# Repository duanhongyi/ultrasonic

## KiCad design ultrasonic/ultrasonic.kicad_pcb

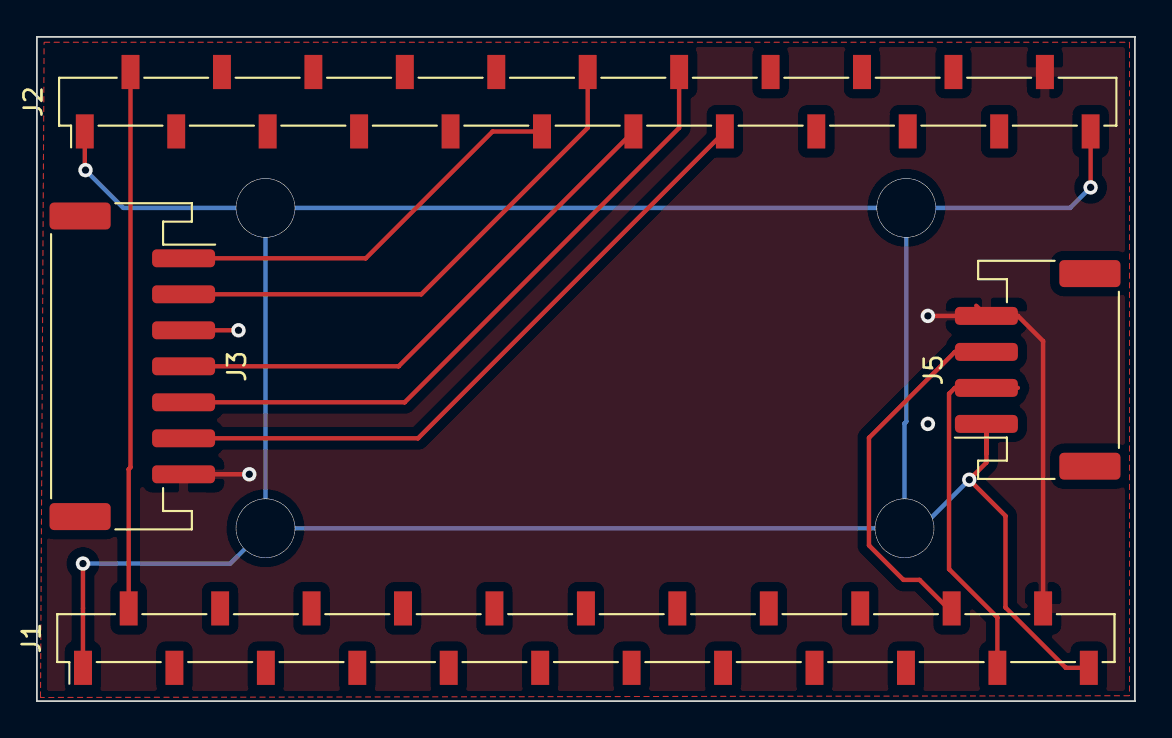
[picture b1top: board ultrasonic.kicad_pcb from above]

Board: 2 copper layers, 61.0 x 36.9 mm, 4 parts (0 on the bottom side), 10 nets.

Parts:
J1, J2: Conn_01x23_Female; PinSocket_1x23_P2.54mm_Vertical_SMD_Pin1Left
J3: Conn_01x07_Female; JST_PH_S7B-PH-SM4-TB_1x07-1MP_P2.00mm_Horizontal
J5: Conn_01x04_Male; JST_PH_S4B-PH-SM4-TB_1x04-1MP_P2.00mm_Horizontal

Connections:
+3V3: J1.2, J2.2
+5V: J1.22, J2.22, J3.7, J5.4
/IO17: J1.20, J5.3
/IO18: J1.21, J5.2
/IO35: J2.15, J3.6
/IO36: J2.14, J3.5
/IO37: J2.13, J3.4
/IO38: J2.12, J3.2
/IO39: J2.11, J3.1
GND: J1.1, J1.23, J2.1, J2.23, J3.3, J5.1

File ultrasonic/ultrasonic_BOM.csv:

"Comment","Description","Designator","Footprint","LibRef","Pins","Quantity","PartNumber","url",
"Conn_01x23_Female","desc","J1,","PinSocket_1x23_P2.54mm_Vertical_SMD_Pin1Right","libref","23","1","","",
"Conn_01x23_Female","desc","J2,","PinHeader_1x23_P2.54mm_Vertical_SMD_Pin1Left","libref","23","1","","",
"Conn_01x07_Female","desc","J3,","JST_PH_S7B-PH-SM4-TB_1x07-1MP_P2.00mm_Horizontal","libref","9","1","","",
"Conn_01x04_Male","desc","J5,","JST_PH_S4B-PH-SM4-TB_1x04-1MP_P2.00mm_Horizontal","libref","6","1","","",

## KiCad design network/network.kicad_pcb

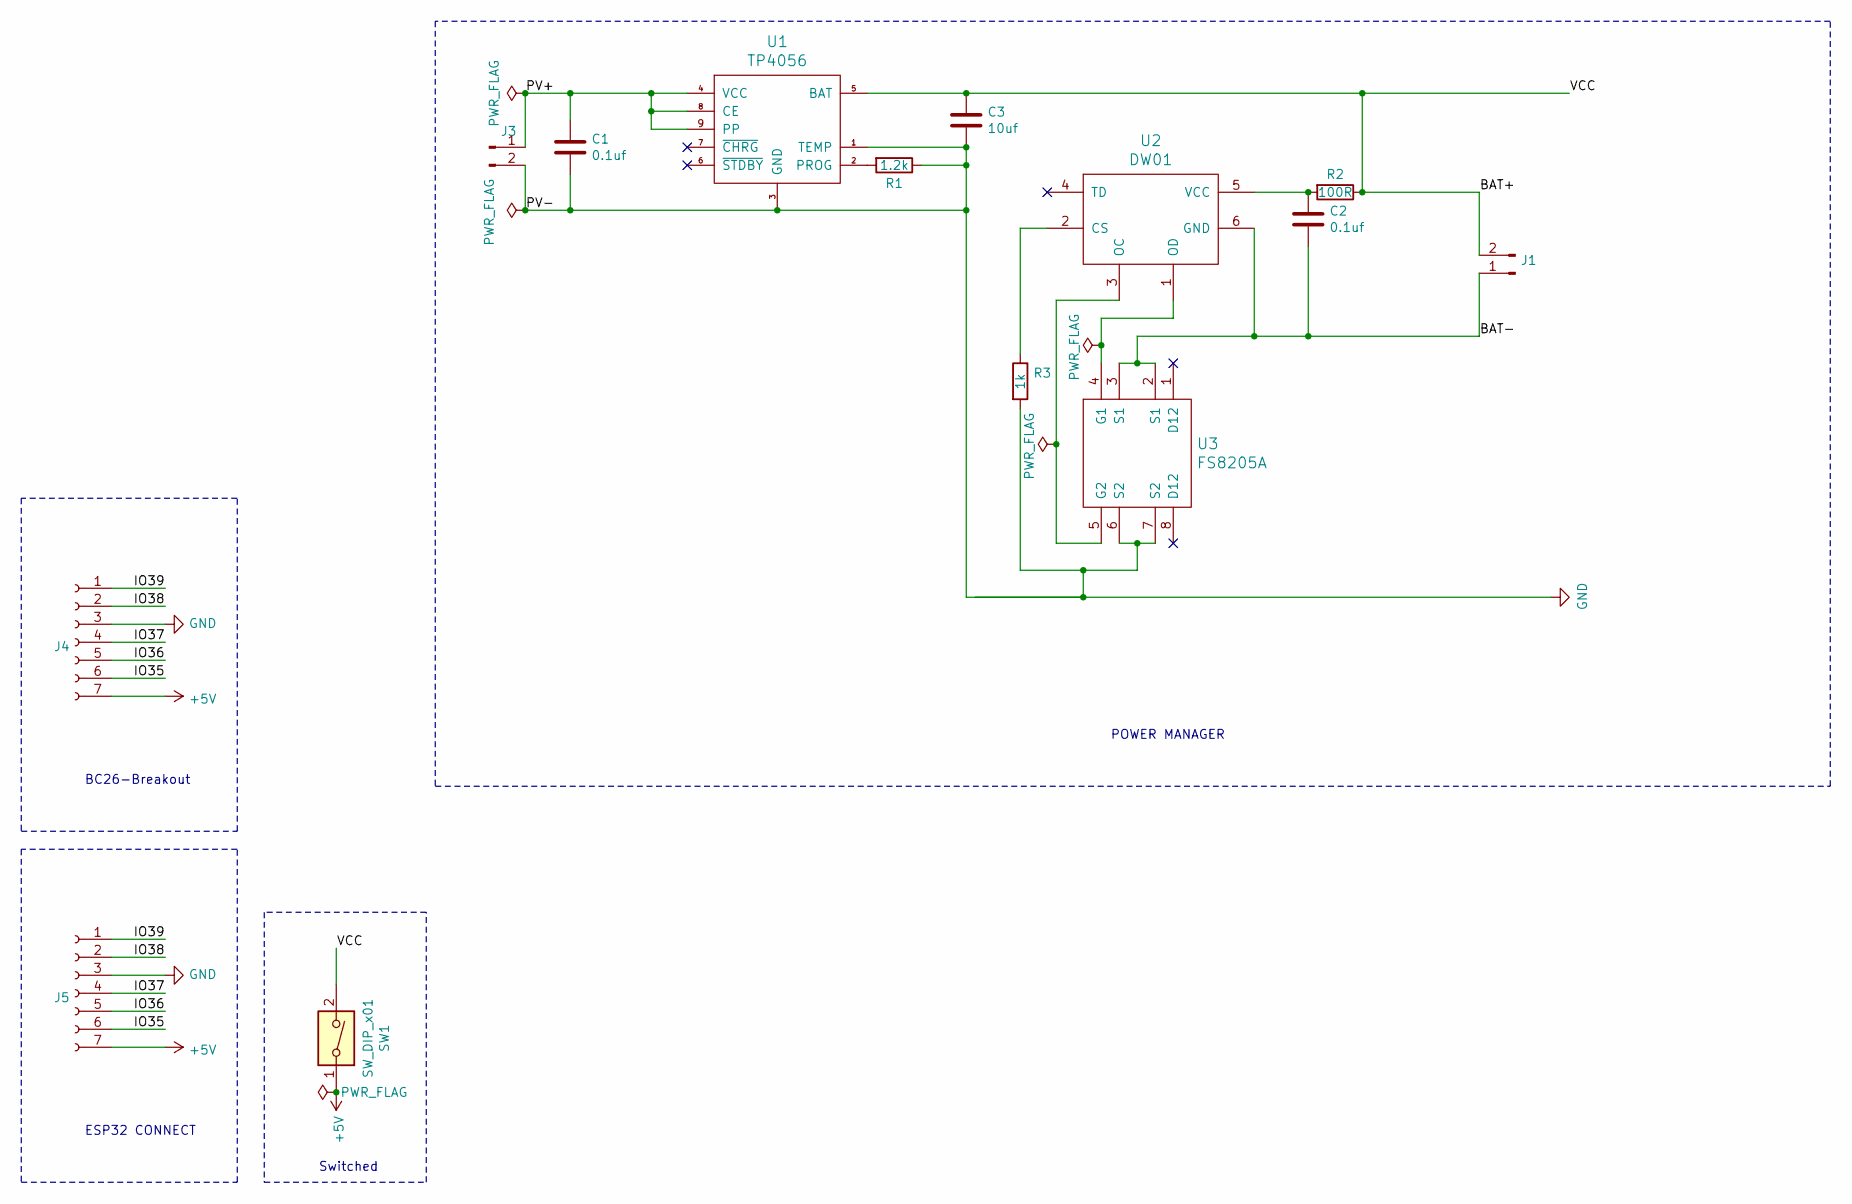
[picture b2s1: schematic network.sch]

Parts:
C1, C2: 0.1uf; C_0603_1608Metric
C3: 10uf; C_0603_1608Metric
J1, J3: Conn_01x02_Male; JST_PH_S2B-PH-SM4-TB_1x02-1MP_P2.00mm_Horizontal
J4: Conn_01x07_Female; PinSocket_1x07_P1.00mm_Vertical_SMD_Pin1Left
J5: Conn_01x07_Female; JST_PH_S7B-PH-SM4-TB_1x07-1MP_P2.00mm_Horizontal
R1: 1.2k; C_0603_1608Metric
R2: 100R; C_0603_1608Metric
R3: 1k; C_0603_1608Metric
SW1: SW_DIP_x01; SW_SPDT_CK-JS102011SAQN
U1: TP4056; TP4056_SOP-8-PP
U2: DW01; SOT-23-6_Handsoldering
U3: FS8205A; TSSOP-8_4.4x3mm_P0.65mm

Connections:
+5V: J4.7, J5.7, SW1.1
/BAT+: C3.1, J1.2, R2.1, SW1.2, U1.5 (BAT)
/BAT-: C2.2, J1.1, U2.6 (GND), U3.2 (S1), U3.3 (S1)
/IO35: J4.6, J5.6
/IO36: J4.5, J5.5
/IO37: J4.4, J5.4
/IO38: J4.2, J5.2
/IO39: J4.1, J5.1
/PV+: C1.1, J3.1, U1.4 (VCC), U1.8 (CE), U1.9 (PP)
GND: C1.2, C3.2, J3.2, J4.3, J5.3, R1.1, R3.2, U1.1 (TEMP), U1.3 (GND), U3.6 (S2), U3.7 (S2)
unnamed: C2.1, R2.2, U2.5 (VCC)
unnamed: R1.2, U1.2 (PROG)
unnamed: R3.1, U2.2 (CS)
unnamed: U2.1 (OD), U3.4 (G1)
unnamed: U2.3 (OC), U3.5 (G2)

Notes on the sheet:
BC26-Breakout
Switched
ESP32 CONNECT
POWER MANAGER

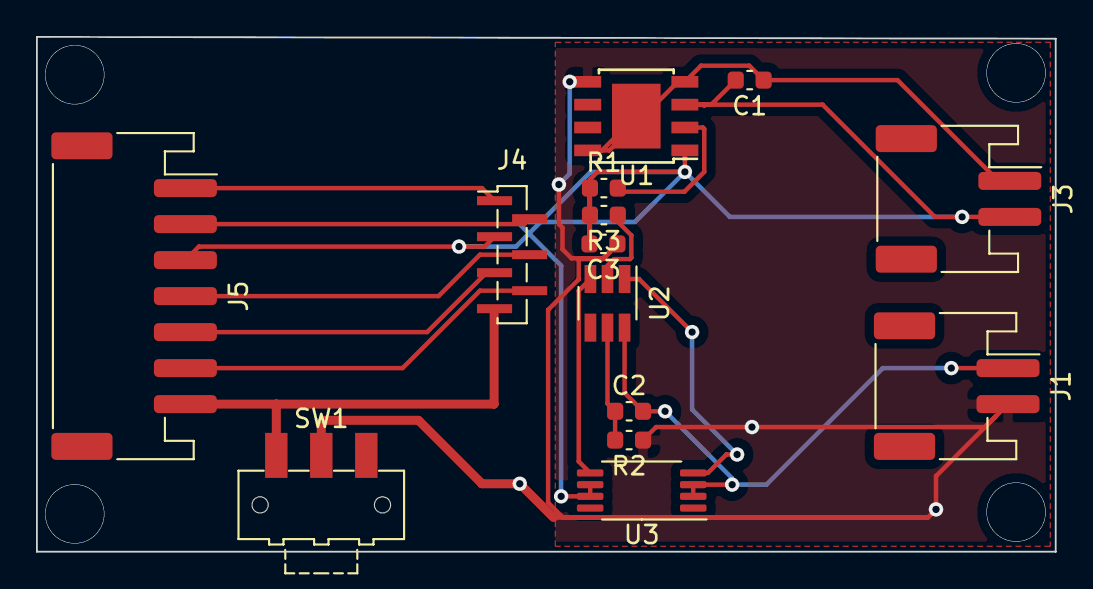
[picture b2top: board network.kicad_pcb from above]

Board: 2 copper layers, 56.6 x 28.6 mm, 14 parts (0 on the bottom side), 15 nets.

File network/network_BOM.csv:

"Comment","Description","Designator","Footprint","LibRef","Pins","Quantity","PartNumber","url",
"0.1uf","desc","C1,C2,","C_0603_1608Metric","libref","2","2","","",
"10uf","desc","C3,","C_0603_1608Metric","libref","2","1","","",
"Conn_01x02_Male","desc","J1,J3,","JST_PH_S2B-PH-SM4-TB_1x02-1MP_P2.00mm_Horizontal","libref","4","2","","",
"Conn_01x07_Female","desc","J4,","PinSocket_1x07_P1.00mm_Vertical_SMD_Pin1Left","libref","7","1","","",
"Conn_01x07_Female","desc","J5,","JST_PH_S7B-PH-SM4-TB_1x07-1MP_P2.00mm_Horizontal","libref","9","1","","",
"1.2k","desc","R1,","C_0603_1608Metric","libref","2","1","","",
"100R","desc","R2,","C_0603_1608Metric","libref","2","1","","",
"1k","desc","R3,","C_0603_1608Metric","libref","2","1","","",
"TP4056","desc","U1,","TP4056_SOP-8-PP","libref","9","1","","",
"DW01","desc","U2,","SOT-23-6_Handsoldering","libref","6","1","","",
"FS8205A","desc","U3,","TSSOP-8_4.4x3mm_P0.65mm","libref","8","1","","",
"Through Hole Items ",
"SW_DIP_x01","desc","SW1,","SW_SPDT_CK-JS102011SAQN","libref","5","1","","",

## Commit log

2021-06-03 init repo
2021-06-09 feat(network): add network
2021-06-10 new release
2021-06-11 change pinhead to left
